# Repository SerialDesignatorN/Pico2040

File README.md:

# Pico2040
RP2040-based dev board designed in KiCad.
## Required libraries (in order to change some items):
- TL3365AF180QG ***(found easily on SnapEDA)***
# Recommended ordering options
For the Pico2040, ordering via JLCPCB is recommended. Here are some recommended settings for ordering from each manufacturer:
## JLCPCB
- Base Material: **FR-4**
- Layers: **2** (do not change)
- PCB Qty: ***up to you (max is 30 to prevent black market revenue)***
- Different Designs: **1** (do not change)
- Delivery Format: **Either *"Single PCB"* or *"Panel by JLCPCB"***
- PCB thickness: **1.6mm**
- PCB color: **Green**
Don't change anything else after the settings I mentioned

## PCBWay
- Board Type: **Single Pieces**
- Different design in panel: **1**
- Quantity: ***up to you (max is 30 to prevent black market revenue)***
- Layers: **2** (do not change)
- Material: **FR-4**
- FR4-TG: **TG150-160**
- Thickness: **1.6mm**
- Min track/spacing: **4/4mil**
- Min hole size: **0.3mm**
- Solder Mask: **Green**
Don't change anything else after the settings I mentioned

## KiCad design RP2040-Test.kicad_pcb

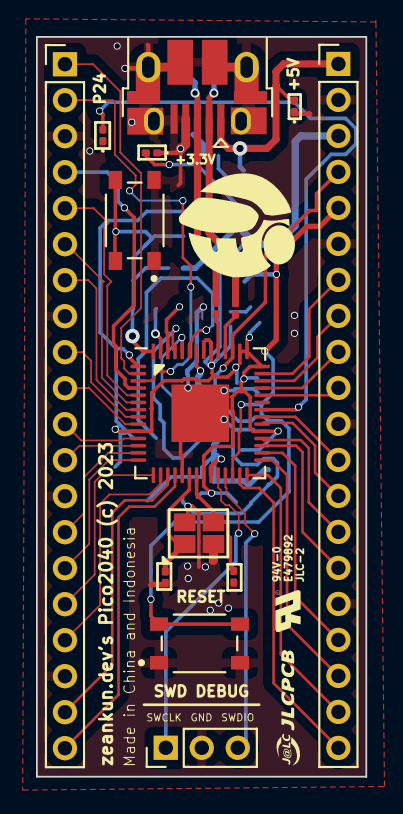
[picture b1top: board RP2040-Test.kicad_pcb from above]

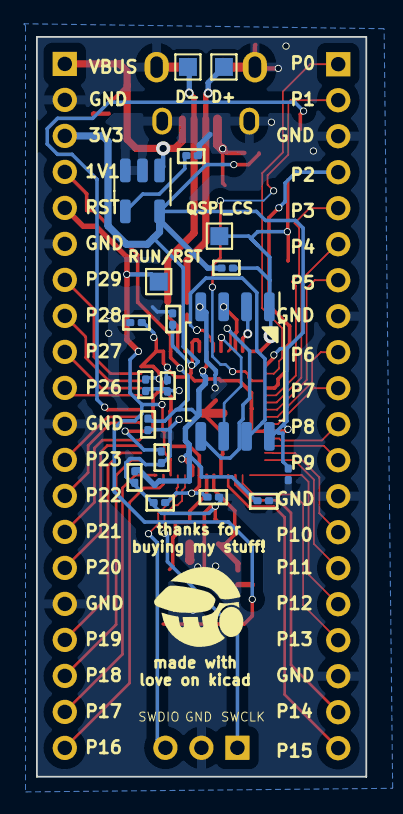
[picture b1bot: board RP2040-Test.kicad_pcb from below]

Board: 2 copper layers, 18.3 x 41.1 mm, 34 parts (19 on the bottom side), 49 nets.

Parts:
C1, C2, C3, C4, C5, C6, C7, C8, C9, C10, C11, C12, C13, C14: C; C_0201_0603Metric
D1, D2, D3: LED; LED_0201_0603Metric
J1: USB_B_Micro; USB_Micro-B_Amphenol_10103594-0001LF_Horizontal
J2, J3: Conn_01x20; PinHeader_1x20_P2.00mm_Vertical
J4: Conn_01x03; PinHeader_1x03_P2.00mm_Vertical
R1, R2, R3: R; R_0201_0603Metric
S1, S2: TL3365AF180QG; SW_TL3365AF180QG
TP1: RESET; TestPoint_Pad_1.0x1.0mm
TP2: USB_DP; TestPoint_Pad_1.0x1.0mm
TP3: USB_DM; TestPoint_Pad_1.0x1.0mm
TP4: BOOTSEL; TestPoint_Pad_1.0x1.0mm
U1: MIC5205-3.3YM5; SOT-23-5
U2: RP2040; QFN-56-1EP_7x7mm_P0.4mm_EP3.2x3.2mm
U3: W25Q32JVSS; SOIC-8_5.23x5.23mm_P1.27mm
Y1: Crystal_GND24_Small; Crystal_SMD_EuroQuartz_X22-4Pin_2.5x2.0mm

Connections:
+1V1: C10.1, C11.1, C12.1, J3.4, U2.23 (DVDD), U2.45 (VREG_VOUT), U2.50 (DVDD)
+3.3V: C2.1, C3.1, C4.1, C5.1, C6.1, C7.1, C8.1, C9.1, D3.2 (A), J3.3, R3.1, U1.5 (OUT), U2.1 (IOVDD), U2.10 (IOVDD), U2.22 (IOVDD), U2.33 (IOVDD), U2.42 (IOVDD), U2.43 (ADC_AVDD), U2.44 (VREG_IN), U2.48 (USB_VDD), U2.49 (IOVDD), U3.8 (VCC)
/GPIO0: J2.1, U2.2 (GPIO0)
/GPIO1: J2.2, U2.3 (GPIO1)
/GPIO2: J2.4, U2.4 (GPIO2)
/GPIO3: J2.5, U2.5 (GPIO3)
/GPIO4: J2.6, U2.6 (GPIO4)
/GPIO5: J2.7, U2.7 (GPIO5)
/GPIO6: J2.9, U2.8 (GPIO6)
/GPIO7: J2.10, U2.9 (GPIO7)
/GPIO8: J2.11, U2.11 (GPIO8)
/GPIO9: J2.12, U2.12 (GPIO9)
/GPIO10: J2.14, U2.13 (GPIO10)
/GPIO11: J2.15, U2.14 (GPIO11)
/GPIO12: J2.16, U2.15 (GPIO12)
/GPIO13: J2.17, U2.16 (GPIO13)
/GPIO14: J2.19, U2.17 (GPIO14)
/GPIO15: J2.20, U2.18 (GPIO15)
/GPIO16: J3.20, U2.27 (GPIO16)
/GPIO17: J3.19, U2.28 (GPIO17)
/GPIO18: J3.18, U2.29 (GPIO18)
/GPIO19: J3.17, U2.30 (GPIO19)
/GPIO20: J3.15, U2.31 (GPIO20)
/GPIO21: J3.14, U2.32 (GPIO21)
/GPIO22: J3.13, U2.34 (GPIO22)
/GPIO23: J3.12, U2.35 (GPIO23)
/GPIO26: J3.10, U2.38 (GPIO26_ADC0)
/GPIO27: J3.9, U2.39 (GPIO27_ADC1)
/GPIO28: J3.8, U2.40 (GPIO28_ADC2)
/GPIO29: J3.7, U2.41 (GPIO29_ADC3)
/QSPI_CS: R3.2, S1.3, S1.4, TP4.1, U2.56 (QSPI_SS), U3.1 (~CS)
/QSPI_SCLK: U2.52 (QSPI_SCLK), U3.6 (CLK)
/QSPI_SD0: U2.53 (QSPI_SD0), U3.5 (DI(IO0))
/QSPI_SD1: U2.55 (QSPI_SD1), U3.2 (DO(IO1))
/QSPI_SD2: U2.54 (QSPI_SD2), U3.3 (IO2)
/QSPI_SD3: U2.51 (QSPI_SD3), U3.7 (IO3)
/RESET: J3.5, S2.3, S2.4, TP1.1, U2.26 (RUN)
/SWCLK: J4.1, U2.24 (SWCLK)
/SWDIO: J4.3, U2.25 (SWD)
/USB_DM: J1.2 (D-), R2.1, TP3.1
/USB_DP: J1.3 (D+), R1.1, TP2.1
/XIN: C14.1, U2.20 (XIN), Y1.3
/XOUT: C13.1, U2.21 (XOUT), Y1.1
GND: C1.2, C2.2, C3.2, C4.2, C5.2, C6.2, C7.2, C8.2, C9.2, C10.2, C11.2, C12.2, C13.2, C14.2, D1.1 (K), D2.1 (K), D3.1 (K), J1.4 (ID), J1.5 (GND), J1.6 (Shield), J2.3, J2.8, J2.13, J2.18, J3.2, J3.6, J3.11, J3.16, J4.2, S1.1, S1.2, S2.1, S2.2, U1.2 (GND), U1.3 (EN), U2.19 (TESTEN), U2.57 (GND), U3.4 (GND), Y1.2, Y1.4
unnamed: D1.2 (A), U2.36 (GPIO24)
unnamed: C1.1, U1.4 (BP)
unnamed: R2.2, U2.46 (USB_DM)
unnamed: R1.2, U2.47 (USB_DP)
VBUS: D2.2 (A), J1.1 (VBUS), J3.1, U1.1 (IN)

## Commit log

2023-08-07 Fixed UL licensing with JLCPCB

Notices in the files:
RP2040-Test.kicad_pcb:
zeankun.dev's Pico2040 (c) 2023
